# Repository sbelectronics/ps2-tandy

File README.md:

# PS/2 Keyboard to Tandy 1000A Computer Converter
## Scott Baker, [http://www.smbaker.com/](http://www.smbaker.com/)

I found a Tandy 1000A on eBay without a keyboard. I grew impatient and wanted to use it.
So I build an adapter to use a PS2 keyboard on a Tandy 1000A.

### Pin Assignments:

    PB0 - PS/2 data
    PB1 - PS/2 CLK
    PB2 - Tandy CLK
    PB3 - Tandy Data
    PB4 - Tandy Busy

### Custom Mappings

Some of the Tandy Keys are different from the PS2 keys...

* PS2 Break - Tandy Break
* PS2 Ctrl-Break - Tandy Break
* PS2 Scroll Lock - Tandy Hold
* PS2 Backslash - Tandy unshifted KP7 or KP4
* PS2 Backquote - Tandy unshifted KP8 or KP2

### Bill of materials:

* X2 ... MINIDIN6_PE ... 6-pin minidin PS/2 jack ... digikey CP-2460-ND (the ones in the prototype came from eBay -- cheaper in quantity)
* X1 ... DIN-8 ... 8 pin din connector ... digikey CP-7080-ND
* U1 ... ATINY85 ... microcontroller ... digikey ATTINY85-20PU-ND
* JP1, JP2 ... 0.100 headers ... any old 0.100 header
* R2, R3 ... 4.7 K resistor
* R7 ... 150 ohm resistor
* C5, C6 ... 0.1uF monolithic ceramic capacitor
* C7, C7_1 ... 0.01uF monolithic ceramic capacitor, optional
* C4 ... 10uF electrolytyic cap, go for 10V or more to be safe
* F1 or F2 ... 1 amp pico-fuse, or a PTC fuse, or just wire it across if you're feeling lucky
* L1, L2 ... 47 microhenry inductor, do not buy, just wire it across

If you want to build yourself an 8-pin DIN cable for connecting the adapter to your Tandy 1000, then also pick up a pair of CP-1080-ND from digikey. You can also buy 8-pin DIN cables premade on ebay and amazon, and this would save you some wiring effort. I made my own. Also note that the 8th (center) pin is not used, so a 7 pin PIN cable may work just as well.

Note on terminology - The "big" round Tandy connectors are DIN connectors. The "small" round PS2 connectors are mini-DIN connectors. So make sure to get yourself the right connectors.

### Programming

I programmed the ATTINY85 using a minipro programmer that I bought on ebay. You'll find two files, one of the files holds the fuses. The other file holds the code. The github repo includes a screenshot of the fuse settings.

### Eagle and Gerber files

These are checked in. Note that the 0.3 design has not been fabricated. It's functionally identical to the 0.1 design that I built in the youtube video, but with obsolete (and occasionally misleading) components removed. I recommend you build the 0.3 design, not the 0.1 design.

Board revisions:

* 0.1 - design used in the video
* 0.3 - a few small issues with silkscreen. Published to github but not produced.
* 0.4 - fixed the silkscreen issues in 0.3; sent this one off to jlcpcb as second prototype (misnamed it as 0.3)

### Attribution:

* PS/2 Keyboard Library

      Interrupts: Interfacing a Microcontroller with a PS/2 Keyboard
      http://www.nerdkits.com/videos/interrupts_and_ps2_keyboard/

### License
Creative Commons Attribution-ShareAlike 4.0 International License (http://creativecommons.org/licenses/by-sa/4.0/)

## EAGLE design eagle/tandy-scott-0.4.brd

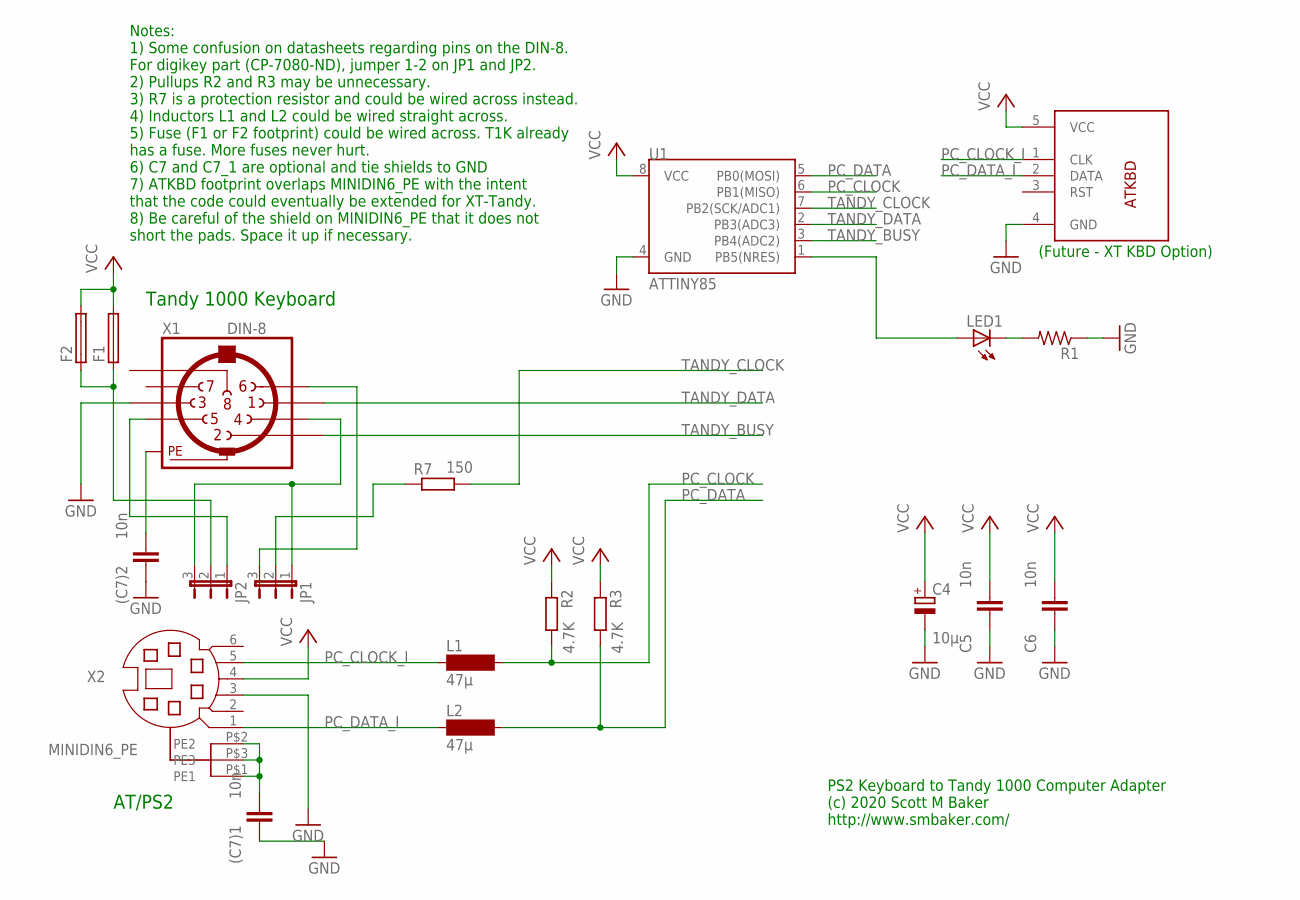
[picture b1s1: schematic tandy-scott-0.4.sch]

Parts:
(C7)1, (C7)2: 10n; C025-025X050
C4: 10µ; E2-5
C5, C6: 10n; C025-025X050
F1: PTC_FUSE0.200; PTC_0.200
F2: PTC_FUSE; PTC_0.400
JP1, JP2: JP2E; JP2
L1, L2: 47µ; SD75
LED1: LED3MM
R1: R-US_0204/7; 0204/7
R2, R3: 4.7K; 0204/7
R7: 150; 0204/7
U1: ATTINY85; DIP08
U$2: ATKBDNOHOLES; DIN_5_FEMALE_SCOTT_DIGIKEY_NOHOLES
X1: DIN-8; SDS-80J
X2: MINIDIN6_PE

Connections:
GND: (C7)1.2, (C7)2.2, C4.-, C5.2, C6.2, R1.1, U1.4 (GND), U$2.4 (GND), X1.3, X2.3
unnamed: (C7)2.1, X1.PE, X1.PE@ (PE)
unnamed: JP2.1, X1.5
unnamed: JP1.1, JP2.3, X1.4
unnamed: LED1.K (C), R1.2
unnamed: JP1.3, X1.6
unnamed: (C7)1.1, X2.P$1 (PE1), X2.P$2 (PE2), X2.P$3 (PE3)
unnamed: LED1.A, U1.1 (PB5(NRES))
unnamed: F1.1, F2.1, JP2.2
unnamed: JP1.2, R7.2
PC_CLOCK: L1.2, R2.1, U1.6 (PB1(MISO))
PC_CLOCK_I: L1.1, U$2.1 (CLK), X2.5
PC_DATA: L2.2, R3.1, U1.5 (PB0(MOSI))
PC_DATA_I: L2.1, U$2.2 (DATA), X2.1
TANDY_BUSY: U1.3 (PB4(ADC2)), X1.2
TANDY_CLOCK: R7.1, U1.7 (PB2(SCK/ADC1))
TANDY_DATA: U1.2 (PB3(ADC3)), X1.1
VCC: C4.+, C5.1, C6.1, F1.2, F2.2, R2.2, R3.2, U1.8 (VCC), U$2.5 (VCC), X2.4

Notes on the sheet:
AT/PS2
Tandy 1000 Keyboard
Notes: 1) Some confusion on datasheets regarding pins on the DIN-8. For digikey part (CP-7080-ND), jumper 1-2 on JP1 and JP2. 2) Pullups R2 and R3 may be unnecessary. 3) R7 is a protection resistor and could be wired across instead. 4) Inductors L1 and L2 could be wired straight across. 5) Fuse (F1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
PS2 Keyboard to Tandy 1000 Computer Adapter (c) 2020 Scott M Baker http://www.smbaker.com/
(Future - XT KBD Option)

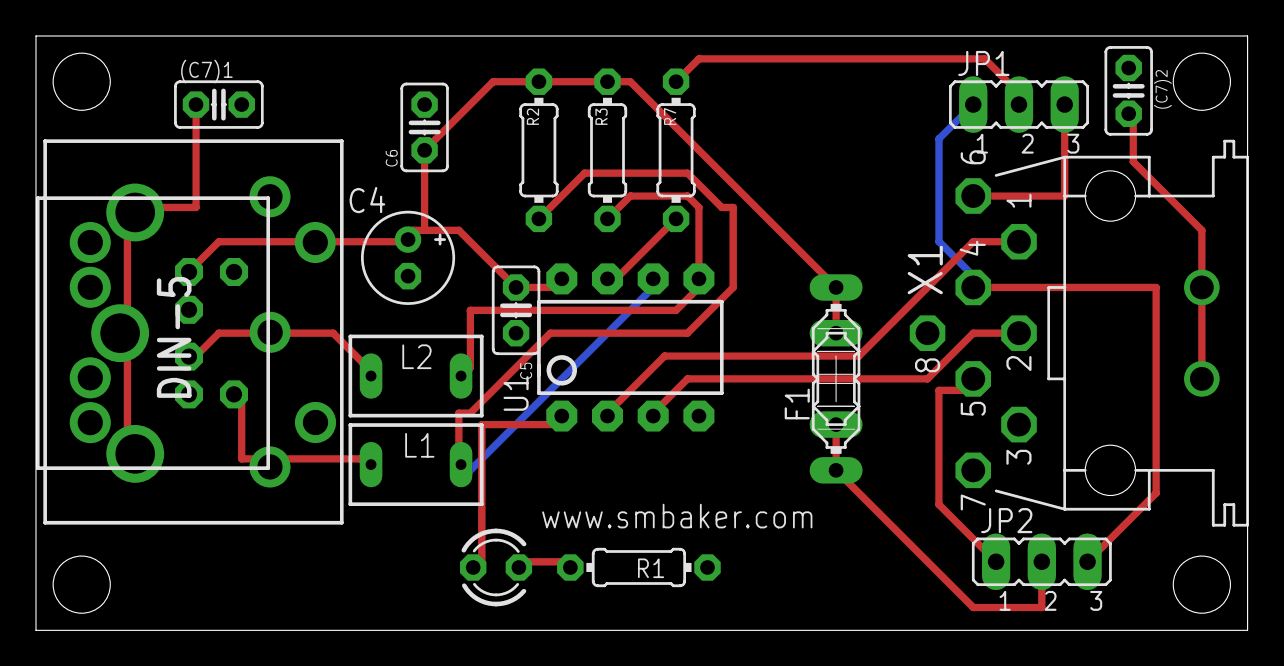
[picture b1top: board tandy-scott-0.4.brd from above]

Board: 2 copper layers, 67.3 x 33.0 mm, 20 parts (0 on the bottom side), 18 nets.

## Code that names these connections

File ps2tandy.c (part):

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#include "tandy_scancode_map.h"

//PIN configuration
//PB4          -  Tandy Busy
//PB3          -  Tandy Data
//PB2          -  Tandy CLK
//PB1 (PCINT1) -  PS2 Keyboard CLK
//PB0          -  PS2 Keyboard DATA

#define TANDY_BUSY (1<<PB4)
#define TANDY_DATA (1<<PB3)
#define TANDY_CLK  (1<<PB2)

#define TANDY_CLK_LOW PORTB &= ~TANDY_CLK
#define TANDY_CLK_HIGH PORTB |= TANDY_CLK
#define TANDY_DATA_LOW PORTB &= ~TANDY_DATA
#define TANDY_DATA_HIGH PORTB |= TANDY_DATA

#define PS2_CLK (1<<PB1)
#define PS2_DATA (1<<PB0)

#define PS2_CAPSLOCK_SCANCODE 0x58
#define PS2_NUMLOCK_SCANCODE 0x77
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ISR(PCINT0_vect){

  //make sure clock line is low, if not ignore this transition
  if(PINB & (1<<PB1)){
    return;
  }

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
  //if we have not started, check for start bit on DATA line
  if(!started){
    if ( (PINB & (1<<PB0)) == 0 ) {
      started = 1;
      bit_count = 0;
      kbd_data = 0;
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  } else if(bit_count < 8) { //we started, read in the new bit
    //put a 1 in the right place of kdb_data if PC2 is high, leave
    //a 0 otherwise
    if(PINB & (1<<PB0)){
      kbd_data |= (1<<bit_count);
    }
    bit_count++;
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
void led_init()
{
  // make pb5 an output
  DDRB |= (1<<PB5);
}

void led_on()
{
  PORTB |= (1<<PB5);
}

void led_off()
{
  PORTB &= ~(1<<PB5);
}

uint8_t read_char(){
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  ack_event = 0;
  nak_event = 0;

  //make PB1 input pin
  //DDRB &= ~(1<<PB1);
  //turn on pullup resistor
  PORTB |= (1<<PB1);

  //Enable PIN Change Interrupt 1 - This enables interrupts on pins
  GIMSK |= (1<<PCIE);

  //Set the mask on Pin change interrupt 1 so that only PCINT1 (PB1) triggers
  //the interrupt.
  PCMSK |= (1<<PCINT1);
}
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
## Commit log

2020-05-07 initial checkin
2020-05-07 fix the readme
2020-05-07 fix the readme better
2020-05-16 get tilde,backslash,break keys all working
2020-05-17 check in gerbers and eagle files
2020-05-17 check in fuse screenshot, update readme
2020-05-17 add note about din connectors to readme
2020-05-24 board revision 0.4; second jlcpcb prototype

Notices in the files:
parts and their libraries:
SparkFun-DigitalIC: Licensing: Creative Commons ShareAlike 4.0 International - https://creativecommons.org/licenses/by-sa/4.0
